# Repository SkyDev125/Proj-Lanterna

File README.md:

# Proj-Lanterna
# Simulação multisim: https://www.multisim.com/content/cTWDcsQrontshF9KCvqVsF/lanterna_elf09/
# Simulação Tinkercad: https://www.tinkercad.com/things/1mGMwoa5kaB
# NOTA - quando abrir o ficheiro EAGLE .brd, o pouring do cobre não será visivel (o shielding). É necessário clicar no ratsnest para fazer o pouring do cobre e assim o shielding será visivel. Nas imagens aqui adicionadas na pasta "Images" é visivel o shielding, sendo que já fiz esse processo posteriormente.
# NOTA2 - Foi possivel descobrir como delimitar a area do pouring do cobre (shielding) para assim poder deixar um shielding mais apelativo!
# Trabalho de ELF09 completo com sucesso no melhor que foi possivel!

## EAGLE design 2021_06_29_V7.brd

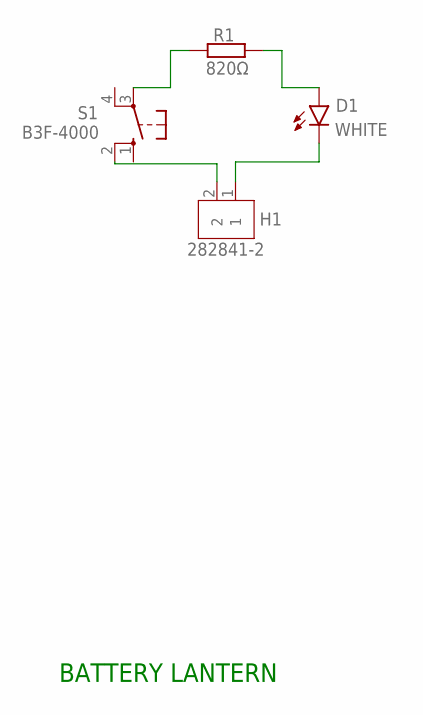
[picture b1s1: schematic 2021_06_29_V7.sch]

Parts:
D1: WHITE; LEDRD254W60D565H860B_W
H1: 282841-2; TERMBLK_508-2N
R1: 820Ω; 0207/7
S1: B3F-4000; B3F-40XX

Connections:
unnamed: H1.2, S1.2 (S1)
unnamed: R1.1, S1.3
unnamed: D1.1 (A), R1.2
unnamed: D1.2 (C), H1.1

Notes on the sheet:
BATTERY LANTERN

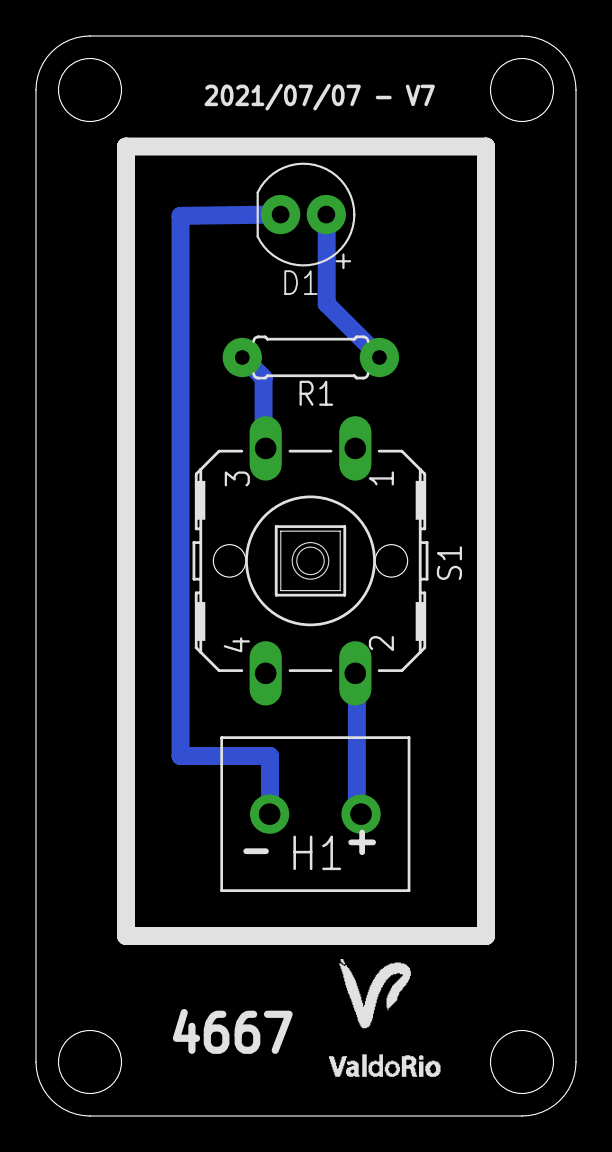
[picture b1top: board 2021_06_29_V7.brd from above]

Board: 2 copper layers, 30.0 x 60.0 mm, 4 parts (0 on the bottom side), 4 nets.

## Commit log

2021-07-07 V7 files
2021-07-09 Adding all files of the final version
